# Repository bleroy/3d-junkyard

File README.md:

# 3d-junkyard

A repository of various 3D models and projects.

So far:

* [DecentXE](./DecentXE): a mechanical keyboard for Atari XE computers
* [DecentXL](./DecentXL/): a mechanical keyboard for Atari 600XL and 800XL computers
* [Decent400](./Decent400/): a mechanical keyboard for Atari 400 computers
* [Decent800](./Decent800/): a mechanical keyboard for Atari 800 computers
* [Decent1200](./Decent1200/): a mechanical keyboard for Atari 1200XL computers 
* [Dungeon Master](./DungeonMaster): reverse-engineering Dungeon Master's rendering and running it in a browser
* [Beyond the Jaggi lines](./Jaggilines): reverse-engineering Rescue on Fractalus and running it in a browser
* [JoyKeyMX](./JoyKeyMX): a joypad compatible with Atari 8-bit and 7800 built with Cherry MX compatible switches

## License

All hardware in this repository is licensed under [CERN Open Hardware License v2](https://ohwr.org/cern_ohl_p_v2.pdf).
All software in this repository is licensed under the [MIT license](https://mit-license.org/).
All documentation in this repository is licensed under [Creative Commons Creative Commons Attribution-ShareAlike 4.0 International Public License](https://creativecommons.org/licenses/by-sa/4.0/legalcode).

Full terms can be found in the [LICENSE](./LICENSE) file or on the web sites linked above.

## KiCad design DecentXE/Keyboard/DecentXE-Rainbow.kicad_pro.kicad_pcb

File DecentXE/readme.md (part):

# Decent XE mechanical keyboard replacements for Atari XE computers

Whether you have an old Atari XE computer with a dead keyboard membrane, would like to use a XE keyboard with your favorite PC emulators, or just want to build a more modern XE keyboard, this is the project for you.

There are two versions of the keyboard: modern and vintage. Modern uses brand new MX-compatible key caps, while vintage uses the original Atari key caps and adapts them to modern switches.

There's been a number of previous projects to put a modern keyboard on Atari 8-bit computers. I don't think anyone's done it while preserving the original keycaps though (would love to be proven wrong). Once assembled, you can't tell the difference from an aesthetic point of view... Check this out:

But wait!... That's not all. Since the project started, there's been multiple revisions, adaptations to all kinds of demands from other Atari enthusiasts, and you now have many options to build the keyboard of your dreams...

## Current version

The current revision of the DecentXE modern keyboard is: **rev. 16.1**.

## Can I buy one?

The project is open-source, and I'm encouraging everyone to try to build their own. I do sell kits and assembled keyboards (both modern and vintage) for those who are not comfortable with ordering parts, PCBs or using a soldering iron. If you'd like to order something, [drop me a personal message on AtariAge](https://forums.atariage.com/profile/76850-screamingattheradio/). Keyboards and kits are made to order, so expect several weeks between ordering and receiving.

How expensive is it? It depends on what you're ordering, but this is a made-to-order custom mechanical keyboard, so, not cheap. You can find all the prices [in this thread](https://forums.atariage.com/topic/352558-decent-xe-mechanical-keyboard-for-atari-xe-computers-how-to-order-one/).

## Project history

My first attempt at this was to replace the stem in a [Kailh Box Pink switch](https://novelkeys.com/collections/switches/products/kailh-box-switches?variant=40598132129959) with a 3D-printed version that replaces the regular MX cap footprint with an Atari XE cap footprint. The modified stems were printed with my first printer, an Elegoo Mars 2 Pro. Its 50 micron resolution was essential when replacing such a small and precise part.

This worked great, with switches that were a little more gritty than the originals but still a huge improvement over the mushy XE keyboard I was replacing.

As I made the project public on [Atariage forums](https://forums.atariage.com/topic/324588-atari-130xe-keyboard-rebuild-vintage-keycaps-on-modern-switches), I quickly discovered the key caps I had on my 130XE were only one of two variants, and not the most common at that. I've been supporting both variants, square and circle ever since.

The stabilizers were costar stabilizers for the left shift, which required some creative bending of the vintage stabilizer rod and always remained a little clunky. The space bar rod has a larger diameter and necessitated 3D-printed stabilizers that were, to be frank, terrible. They sorta did the job, just poorly.

The first plate I made was water-jet-cut steel. That was expensive and rusty. I quickly realized after that first attempt that PCB fabrication houses can make aluminum PCBs for cheap. Those are machined rather than laser or water-jet cut, but the quality is perfectly adequate for a fraction of the price. They are just PCBs without circuitry on them. I later learned how other handmade keyboard makers use the same trick, including with regular PCBs, although aluminum is clearly superior for this application.

The first connector I used was an ad-hoc cable made from breadboard jumper wires (I replaced the notoriously hard to source 24 pin Atari connector with pin headers). Based on early feedback, this was quickly replaced with a choice of standard flat cables, to the 1mm pitch 26 pin FFCs used today. Why 26 pins? Because 24 pin FFC connectors and cables don't exist or are hard to source whereas the 26 pin versions are commonly used in DVD players and printers. Also, that gives us two additional lines to separate the backlighting power from the rest, but that in itself came later, at first there was no backlighting and those two additional lines just duplicated the 5V and ground lines, which was just good practice at the time, but turned out to provide that feature for free later without breaking pinout back-compat.

On the side of the Atari motherboard, an adapter was needed that could plug into the original 24 pin connector or be soldered to pin headers, and had a 1mm pitch 26 pin FFC connector on the other side. The main difficulty is that there's very little space between the motherboard and the bottom of the keyboard.

The next breakthrough resulted from re-thinking the constraints:
* Keep compatibility with vintage key caps
* Keep the assembly the same height as the original so everything looks unchanged, including function keys flush to the case

Keeping the same height with MX switches meant replacing internal parts. This is time-consuming and results in lower-quality. What if instead you could work with lower switches that give enough vertical space to build an interface between the switch and the cap? That's what led me to consider low-profile switches. My first choice was to remain with Kailh switches, that I like quite a lot, and I picked Choc v1, specifically Robins that have a clicking behavior similar to Box Pinks. Using adapters instead of replacing internals however also gave the side benefit to allow people to choose the switches they prefer. If you prefer linear or tactile, that's fine.

I made a new version of the PCB for Choc switches which was also the first to have backlighting.

Then there were demands to support more types of low-profile switches to allow for cheaper alternatives to Kailh Chocs.

Around the same time, I had been trying to find reasonably affordable small batch key cap sets to make it possible to build a keyboard without depending on vintage parts. XLFreak is the one who designed and sourced new key caps from [WASD](https://www.wasdkeyboards.com/) (no longer in activity). The very wide space bar doesn't exist on modern keyboards, so we had to shuffle things around. I think the layout that came out of this is better than the original: we get a larger backspace key, an ISO return key, control moves to the left of the smaller 6.5U space bar, break to its right, caps moves to its modern place above left shift. I was able to lay out the PCB so it's compatible with both the vintage and the modern layouts with a single configuration header.

In order to simplify things and have a single unified PCB design, I designed a switch footprint that could accommodate four different kinds of switches: MX, Kailh Choc, Gateron low-pro and RedDragon low-pro.

I also moved the Raspberry Pi Pico connection off the board to a separate USB adapter board since not everybody needed it and it added routing complexity.

It was also a good time to update the stabilizer design. For modern caps, there was no reason not to use the better alternative that are Durock v2 stabilizers. For vintage caps, I wasn't able to swap left switch stabilizers because the way vintage shift keys are built doesn't leave space for 2U Durock v2 stabilizers.

That was where we were with revision 11, which shipped as a pre-order to readers of [the AtariAge forum thread](https://forums.atariage.com/topic/324588-atari-130xe-keyboard-rebuild-vintage-keycaps-on-modern-switches/).

**Revision 12** moved the FFC connector to the top side of the board so it could be assembled at the fab house with the other surface-mount components, and moved to the bottom-right of the board, next to the break key. The FFC cable is now routed to the front between the two halves of the shield.

The power LED is now surface-mount like the backlight LEDs.

The optional function keys (F1-4) pins are now duplicated on a separate header on the top-right of the board to enable easy wiring of those pins to keys placed for example in an extension device.

The adapter that plugs into the motherboard was now smaller, leaving more space above and removing the requirement to replace the Atari keyboard connector and replace it with pin headers (although that was still recommended). The adapter's FFC connector was now moved to the left of the connector instead of above it.

The plate outline has been modified to let more power LED light through.

The silkscreen has been updated to give clearer instructions about configuring the keyboard for vintage or modern modes.

**Revision 13** changes console keys (Help, Start, Select, Option and Reset) to use low-profile switches, which enables thinner 3D-printed key caps that better fit the XE case.

The PCB now has a visual representation of the keyboard matrix with pin numbers, making debugging easier.

The PCB and plate have a consistent Harry Fatt typeface, and each key gets all its glyphs represented, which makes it easier to use the keyboard without caps.

**Revision 14** replaced the adapter and flat cable with a flexible PCB.

**Revision 15** splits the modern and vintage designs. This removes the requirement to have configuration headers and greatly simplifies the layout of the PCBs. I also stopped building assembled vintage keyboards myself with this version, instead focusing on the higher quality modern keyboards. The files for vintage remain available for thos who want to build their own.

**Revision 16**

[x] Power LED switched to red in BOM
[x] Optional red LED diffuser 3D model
[x] Mid-keyboard support 3D model
[x] Back of the board padding 3D model for better fit in the XE case
[x] Console keys have stabilization holes in PCB and plate
[x] Plate covers the whole width of the keyboard and conoles keys area
[x] PCB made 1.75mm deeper to reach the case's fins on the back of the keyboard area
[x] Remove legends from plate front so it's a uniform black between key caps

**Revision 16.1**

[x] Moved the cable slot and connector apart for easier assembly.
[x] Rerouted the whole thing with wider power tracks.

## Options

### Key caps: vintage or modern?

My own original preference was to use the original key caps from a vintage Atari XE computer. They can be scavenged from an existing computer, or from new old stock that's still available at the usual places. The result is, like above, visually indistinguishable from the original keyboard, but feels oh so much better.

XLFreak has been working on new caps in the style of old Atari caps, but that can be produced in small quantities. The nice thing about those is that no adapter is necessary and the end result is an amazing keyboard that is and feels in every way like a great modern keyboard. This is now my preferred option to upgrade Atari XE keyboards.

### Switches

If you're using modern key caps, you may choose any MX-compatible switch. You'll need 5 low-profile Kailh Choc v1 switches for the conole keys.

If you're using vintage caps, you can pick any Kailh Choc v1 low-profile switch.

## Design

The Decent XE project is built on [an original PCB design](./Keyboard/DecentXE-Modern.kicad_pcb), [a custom aluminum plate](./Plate/DecentXE-plate-modern.kicad_pcb), [MX-compatible switches](https://www.kailhswitch.com/mechanical-keyboard-switches/smt-key-switches/box-blue-white-switches-for-mechanical.html), [Kailh Choc v1 low-profile switches](http://www.kailh.com/en/Products/Ks/CS/), custom key caps, 3D printed adapters and Durock v2 and Costar stabilizers.

Here's [a video showing revision B of the project)](https://youtu.be/r8T07Rskkgs):

And here's [another](https://youtu.be/FDqwOca9oRQ/) showing the revision 11 with modern caps:

## Bill of materials

This project is meant to be reproduced. You'll need a few things that are more or less easy to source, so I've made sure to give multiple roads to success and alternatives for most parts.

It's also an approach that could easily be adapted to other vintage computer keyboards, Atari or not. Everything is provided [under an open source license](../LICENSE) so you're encouraged to reproduce and fork the design.

### Atari XE computer

The project is designed around the conservation of the look of Atari XE computers and the integration of the keyboard in its original case. As such, you'll need a host XE computer to receive the end product.

It is also possible however to build and use this keyboard and use it with an emulator on a PC or Mac through a USB adapter. In this way, you can get closer to the original experience even if you don't have access to the original hardware.

* Optimal: Atari XE computer
* Fine: a PC, mac or a MiSTer with [an emulator](https://www.virtualdub.org/altirra.html)

### Key caps

The best result will be obtained with new key caps.

Key caps can be sourced from [ThockFactory](https://thockfactory.com/fr/configurator) or [GoblinTech](https://goblintechkeys.com/collections/60-keycap).

#### ThockFactory

Use the following configuration files in the ThockFactory configurator:

* [Modern layout (white)](./Caps/Atari%20XE%20-%20White%20-%20Thock.json)
* [Modern layout (Falcon)](./Caps/Atari%20XE%20-%20Falcon%20-%20Thock.json)

#### GoblinTech

Use the following templates when ordering from GoblinTech:

* 
* 

#### Vintage

Vintage key caps from an Atari XE computer can also be used to maintain a look that is indistinguishable from the original. Old-new stock of XE keyboards is also currently available without too much trouble and for a reasonable price.

* Optimal: MX-compatible set of key caps
* Fine: vintage set of XE key caps

### Console keys (Help, Start, Select, Option, Reset)

If you're using modern key caps, you'll need to make a choice for console keys.

The best solution is to re-use your vintage console keys with adapters.

Itś also possible to [3D-print your own](./Caps/fn-console-set-choc.stl) and then paint them. I recommend [Tamiya Sea Grey model paint](https://www.tamiyausa.com/shop/acrylic-paint-flat-mini-10ml/acrylic-mini-xf-83-m-sea-gray/) for a pretty good match with the Atari XE case color. You can mask the legends when painting to make them stand out.

* Fine: 3D-printed
* Optimal: vintage function keys on adapters

### Switches

A choice of switches is highly personal and there are many options. Get a sample set if you don't have a preferred kind. You can choose between MX-compatible switches for modern caps and any Kailh Choc v1 switch for conole switches or for the vintage version.

There are three main categories for switches:
* linear (such as reds): the resistance from the switch is about constant as it's pressed.
* tactile (such as browns): there's a slight bump of resistance as the switch is pressed, giving more feedback than linear switches.
* clicky (such as whites): there's a bump in resistance (or it feels like thereś one), accompanied with an audible and satisfying clicking sound.

Console keys should now be mounted on Kailh Choc v1 low-profile switches, so you'll need to buy 5 that match the characteristics of your main keyboard choice (clicky, linear or tactile).

* Optimal: 57 MX-compatible switches of your preferred brand and kind (for modern caps) + 5 Kailh Choc v1 switches for the console keys
* Fine: 62 Kailh Choc v1 low-profile switches (for vintage caps)

### Adapters

The switch adapters link vintage caps to modern switches. As such, you don't need them if you opted for all modern caps. If you're using vintage console keys, you'll need 5 adapters.

The best option today is to simply have the adapters printed, for example by JLCPCB.

Online printing services have become very inexpensive, and the quality of their prints can't be rivalled by any hobbyist printer available today. The trick for small parts such as these adapters is to group them in [batches](./Stems/kailh-choc-to-xe-circle-set.stl) so they count as a single part. I stopped printing locally after the prototyping phase, and am now ordering all my 3D prints from JLCPCB.

If you decide to print them, you'll need a resin printer with a resolution of 50 micrometers (1/20th of a millimeter) or better.

The choice of resin is very important, as the same design on the same printer can give wildly varying qualities of print. For instance, I stay away from all grey Elegoo resins, as I found them to blur the design and be very unreliable. The resin I've had the best results with is Elegoo's [clear red](https://www.elegoo.com/collections/resin/products/elegoo-standard-resin?variant=32365787807792). Resin prints also tend to be brittle, and it's no fun trying to remove a broken leg from inside a switch's stem or a key cap.

There are adapters in the repo for all types of vintage XE caps. You can even generate your own by using [the OpenScad model](./Stems/keeb-stem.scad), which is fully parametric.

* Optimal: order from a fab house such as JLCPCB
    - 7x [set of circle adapters](./Stems/kailh-choc-to-xe-circle-set.stl) or 7x [set of square adapters](Stems/kailh-choc-to-xe-square-set.stl) if you're going full vintage.
    - 5 adapters, circle or square. You can use one of the sets above (10 adapters per set).
* Fine: print your own with a resin printer

I also sell adapters separately from keyboards.

### Board padding (obsolete as of rev. 16)

For the most stable results, you can add two [padding 3D-printed parts](./Stabilizers/HeightPadding.stl) on top of the main board at the bottom left and right:

Those can be printed on any 3D printer as they don't require a lot of precision.

[Additional padding](./Misc/XE-rev-before-16-depth-padding.stl) can be added to the back of the board to prevent the keyboard from moving to the back of the computer.

### Mid-keyboard support

While the XE case provides some support to the middle of the keyboard with a column, pressing the console keys can still cause some bending of the board. To prevent that, [support](./Misc/XE-mid-keeb-support.stl) can be added to the left of the console keys.

### Power LED coloring

If you have a board with a white power LED and your XE case has a transparent LED window, you can still make thepower LED shine red using a [LED diffuser](./Misc/LED-red-lens.stl) printed in transparent red.

### Stabilizers

If you're using modern caps, just use Durock v2 stabilizers for backspace, Return, left shift and the space bar.

The Atari XE keyboard has stabilizers on the left SHIFT key and on the space bar. Some versions also have stabilizers on control and right shift, but anything 2U and smaller can work well without stabilizers.

The left shift stabilizer is made with a standard metal bar that fits in standard costar stabilizers, for which the vintage plate is designed. There are two possible orientations for the costar stabilizers that work best for the circle and square variants of vintage key caps. Those stabilizers can be bought for a very reasonable price from many places.

The vintage space bar can use Durock v2 stabilizers, for which I've made adapters for both types of vintage Atari space bars.

* Optimal (modern caps): 1x 6.5U and 3x 2U Durock v2 stabilizers
* Fine (vintage caps):
    * Vintage Atari XE left shift stabilizer metal part
    * 2x standard costar stabilizers
    * 1x 6.5U Durock v2 stabilizer set
    * 3D-printed stabilizer adapters [for circle](./Stabilizers/durock-v2-spacebar-circle-adapter.stl) or [square](./Stabilizers/durock-v2-spacebar-square-adapter.stl)

### Main board

The [DecentXE KiCad project](./Keyboard/DecentXE-Modern.kicad_pcb) should have everything you need to order a 2 layer PCB from any manufacturing house. The board requires surface-mount diodes, LEDs, resistors and connectors that are best assembled at the fabrication house: nobody wants to solder 62 of the same very tiny components by hand. I think. I don't.

* Optimal:
    - [DecentXE Modern main board Gerber files](./Keyboard//production/Decent_XE_Keyboard_-_Modern_16.1.zip)
    - [DecentXE Modern BOM file](./Keyboard/production/Decent_XE_Keyboard_-_Modern_16.1-bom.csv)
    - [DecentXE Modern Position file](./Keyboard/production/Decent_XE_Keyboard_-_Modern_16.1-positions.csv)
* Fine:
    - [DecentXE Vintage main board Gerber files](./Keyboard//production/Decent_XE_Keyboard_-_Vintage_15.zip)
    - [DecentXE Vintage BOM file](./Keyboard/production/Decent_XE_Keyboard_-_Vintage_15-bom.csv)
    - [DecentXE Vintage Position file](./Keyboard/production/Decent_XE_Keyboard_-_Vintage_15-positions.csv)

### Plate

While it is possible to build and operate a keyboard without a plate, it will not be as nicely aligned and won't feel as solid as it would with a proper plate.

In terms of weight, the keyboard assembled with an aluminum plate is about 430g.

* Optimal: 1.6mm aluminum PCB. Aluminum PCBs can be made for similar prices as regular PCBs nowadays, and that constitutes the best price / performance compromise currently available.
    - [DecentXE Modern aluminum plate Gerber files](./Plate/production/Decent_XE_Keyboard_Plate_-_Modern_16m.zip)
    - [DecentXE Vintage aluminum plate Gerber files](./Plate/production/Decent_XE_Keyboard_Plate_Vintage_15v.zip)
* Great but expensive: laser-cut or waterjet-cut metal
* Not fine: laser-cut acrylic. Really, don't even try, it'll shatter. Some other laser-cut plastics may be OK, but I can't help you with that, I don't know.

When using vintage caps, you may need to add some spacers between the board and the plate while building, in addition to the switches themselves. I've been using stacked washers.

There's a smaller, 3D-printed plate for the console keys that also adjusts the height of the switches relative to the PCB:

* [Console key plate](./Stabilizers/LowProRaiserPlate.stl)

### Connector

The original Atari XE keyboard's connector was just a part of the mylar membrane. We need a replacement for that. Note that the clearance between the Atari XE motherboard and the bottom of the keyboard is very small at about 16mm.

The current solution is a custom flexible PCB that can plug directly into the Atari motherboard connector, and is compatible with a modern 1mm 26 positions surface-mounted connector on the other side:

If your Atari connector is damaged, or you don't have one, it's also possible to solder [an adapter](../Atari130MX/Atari130MX-adapter/Atari130MX-adapter.kicad_pro) and use a standard 1mm pitch 26 position flat cable.

* Optimal:
    * [Flexible PCB](../DecentXL/DecentXL-Cable/production/DecentXL_Flexible_Cable_2.zip).
* Fine:
    * [FFC 26 position 1mm Type A](https://www.digikey.com/en/products/detail/adafruit-industries-llc/5386/16129671?s=N4IgTCBcDaIIwFsEAIAOBLALgYwBbLADY10A7EAXQF8g) (contacts on the same side on both ends) ribbon cable, 15cm at least.  Here's also [an Amazon source](https://www.amazon.com/uxcell-Flexible-Cable-Ribbon-Player/dp/B07RWRX6YT/r).
    * [XE keyboard Adapter](../Atari130MX/Fabrication/DecentXE-adapter.zip)
    * 1x24 2.54mm pin headers

## Fabrication and assembly instruction

Once you've sourced all the components, it's time to assemble. The following instructions attempt to reflect all the choices you may have made in selecting components.

Jan Beta has a great video where he shows the full assembly process (the mistake he makes with the config jumpers can no longer be made: those are gone from the design).

### Printing console caps and adapters (optional)

There are two known shapes of vintage key caps, requiring distinct adapters. The first type of key cap has square stems, while the second has circular stems.

In this repository, you'll find [OpenScad](./Stems/keeb-stem.scad) and [STL](./Stems) files for [both](./Stems/kailh-choc-to-xe-circle-set.stl) [types](./Stems/kailh-choc-to-xe-circle-set.stl) of stems. If you need to modify anything about the stems, you'd need to regenerate the STL from the OpenScad file. There is [a single OpenScad file](./Stems/keeb-stem.scad) that covers both types of stems through configuration. Otherwise, just send the STL file to your 3D printing manufacturer.

You'll need 62 adapters total for the whole vintage keyboard, and only 5 for modern if you want to re-use your vintage console keys.

### Optional: replace the Atari connector

If you lack the original Atari connector on your motherboard (rare), you may want to use an adapter and solder that in.

### Installing a modern keyboard (assembled)

I do sell assembled modern keyboards, but you still need to get those into your Atari. This section goes through the details of doing that.

The FFC cable should already be attached to the keyboard.

[skip to the common section](#common-section-inserting-the-adapter)

### Installing a vintage keyboard (assembled)

Use a key cap extractor to remove the keys from your vintage keyboard (a key extractor is the best way to make sure you don't damage the caps). Make sure to be especially gentle if you have the square variant, those break easily.

Put the two space bar stabilizer adapters into your vintage space bar. You can set aside the old metal rod for this key, you won't need it. The alignment of the stabilizers and the adapters is not always perfect. If that's a problem in your build, you can try to adjust the OpenScad model to move the footprint and better align with your space bar. Even with good alignment, I recommend salvaging the spring from the original keyboard and inserting it into the new keyboard. It does make a big difference for vintage builds.

Remove the stabilizer rod for your left shift key. You'll need to slightly bend this so it can go around the new switch and into the new stabilizer. This may require some fiddling. In the worst case, the left shift stabilizer can be omitted if you can't find a way to make it work. This is my least favorite part of those keyboards...

Assemble the caps back onto the new keyboard by gently pressing them into place.

[skip to the common section](#common-section-inserting-the-adapter)

### Modern keyboard (kit)

If you ordered a kit or parts from the BOM, there is a specific order in which you should assemble.

#### Assemble the Durock stabilizers

The stabilizers consist of a larger part that has the threaded part, a smaller part that slides into the previous one, a metal bar linking two assemblies of the two previous parts, and some hardware. The stabilizers are best assembled in this order: slide the smaller part into the larger one (make sure you orient it properly), then insert one end of the metal rod into that assembly and push it into place so it clicks and is properly secured. Once you've done that with both ends of the stabilizer, you should be able to verify both ends lift together and with no friction (some people like to lube their stabilizers for added smoothness).

Once the stabilizers are assembled, you can put them in their respective places on the top side of the PCB. Insert the bottom, non-threaded part first, try to lay the stabilizer's surface flat on the PCB, and push the top threaded part into place. This usually moves the other end a bit, so make sure both ends are properly inserted all the way into the holes in the PCB.

Turn the PCB over. Optionally position a small washers around each of the screw holes for the stabilizers. Secure the stabilizer into place with a screw. Repeat this for the space stabilizer, the left shift, the delete key and the return key.

#### Solder the console key switches

The console key switches go *under* the plate, and as such need to be soldered before the other switches are inserted into the plate and soldered.

#### Add the cable

Insert the flexible PCB from below the PCB into its slot through the PCB, so the contacts are on the bottom and can face the board.

Pull the two tabs for the connector, then insert the contacts into the connector, pushing the cable as far as it will go. Push the tabs back in.

At this point, I usually test continuity between a few of the solder points on the board to the other end of the connector, in order to check the cable is properly inserted and secure.

#### Mount the switches onto the plate

Insert switches into the aluminum plate with the LED window to the back and the pins to the front. The exception to this is the modern return key that should have its LED window to the left and pins to the right.

Note that the console keys do not have a place on the plate. That's because they use low-profile switches that wouldn't reach the height of the plate. We'll assemble those later.

#### Get the plate and PCB together

After making sure all the switch pins are vertical and none are bent out of place, carefully align the plate and switches with the stabilizers and the PCB. Slowly and carefully complete that assembly, making sure no pins get bent. Once that is done, the plate and PCB should be a few millimeters apart, more or less evenly spaced across the whole surface. You may want  to secure them together with tape or clothespins until you've soldered enough of them.

#### Solder the switches onto the PCB.

Solder each switch onto the PCB.

Once you've done all the full-size switches, insert the low-profile switches for the console keys into their 3D-printed plate, then align that to the PCB. Solder the switches.

Even after soldering, you can make small adjustments by melting the solder around one of the pins and carefully moving the switch, then reflow the other pin of the same switch to relieve constraints or further adjust.

[skip to the common section](#common-section-inserting-the-adapter)

### Vintage keyboard (kit)

If you ordered a kit or are building one from parts from the BOM, there is a specific order in which you should assemble.

#### Assemble the space stabilizer

Assemble the space stabilizer. The stabilizers consist of a larger part that has the threaded part, a smaller part that slides into the previous one, a metal bar linking two assemblies of the two previous parts, and some hardware. The stabilizers are best assembled in this order: slide the smaller part into the larger one (make sure you orient it properly), then insert one end of the metal rod into that assembly and push it into place so it clicks and is properly secured. Once you've done that with both ends of the stabilizer, you should be able to verify both ends lift together and with no friction (some people like to lube their stabilizers by the way).

Once the stabilizer is assembled, you can put both ends in their respective places on the top side of the PCB. Insert the bottom, non-threaded part first, try to lay the stabilizer's surface flat on the PCB, and push the top threaded part into place. This usually moves the other end a bit, so make sure both ends are properly inserted all the way into the holes in the PCB.

Turn the PCB over. Optionally position a small washers around each of the screw holes for the stabilizers. Secure the stabilizer with a screw.

#### Add the cable

Insert the flexible PCB from below the PCB into its slot through the PCB, so the contacts are on the bottom and can face the board.

Pull the two tabs for the connector, then insert the contacts into the connector, pushing the cable as far as it will go. Push the tabs back in.

At this point, I usually test continuity between a few of the solder points on the board to the other end of the connector, in order to check the cable is properly inserted and secure.

#### Mount the switches onto the plate

Insert switches into the aluminum plate with the LED window to the back and the pins to the front.

#### Get the plate and PCB together

After making sure all the switch pins are vertical and none are bent out of place, carefully align the plate and switches with the stabilizers and the PCB. Slowly and carefully complete that assembly, making sure no pins get bent.

Once that is done, the plate and PCB should be a few millimeters apart, more or less evenly spaced across the whole surface. Low-profile switches have a tendency to not attach to the plate as well as full-sized switches, so don't worry if some of these fall out during assembly, you'll have a chance to set them back in later. At this point, you want to have enough switches in place to ensure proper alignment.

Another thing with low-profile switches is that they're not as good at maintaining the distance between PCB and plate. To make that distane more even with the distance imposed by the space stabilizer, there are two holes for M2 screws at the top of the plate and main board. Use three M2 nuts to keep the correct distance between the plate and PCB. Secure everything from the top with one final nut.

#### Assemble the left shift stabilizer

The left shift stabilizer is more problematic and potentially the most frustrating part of this build. Worst case, it may be fine to just omit this stabilizer because if improperly installed it can make things worse. The stabilizer consists of two plastic parts that should fit into slots around the switch's position. Depending on whether you have circle or square caps, it should be installed upside up or upside down. Those stabilizers are very tricky to put in place. Once they are in place, you'll need (later, we'll get back to that) to get the metal rod from your vintage left shift, remove it, then bend it slightly so it can go around the switch and still be inserted into the new stabilizer. I'm not kidding when I say this is frustrating.

#### Solder the switches

Solder the switches onto the PCB. The Choc switches will barely stick out on the back of the PCB. This is normal, but makes soldering a little more difficult. Give the iron enough time to heat up the vias, the solder and the pins and create a proper join, even if that join ends up relatively flat.

Dont's forget the console keys. Since those do not mount on the plate, use a 3D-printed console key plate to align the switches precisely and keep the switches at the correct height.

Even after soldering, you can make small adjustments by melting the solder around one of the pins and carefully moving the switch, then reflow the other pin of the same switch to relieve constraints or further adjust.

### Common section: inserting the cable

Remove your existing keyboard, pulling the membrane connector carefully using both hands to avoid accidentally folding it.

Insert the flexible PCB into the connector on the motherboard.

Add the height padding on top of your keyboard's main PCB, to the bottom left and right.

You can now power your computer. The power LED on the keyboard should go on and the backlighting should too (this is a good time to set the potentiometer on the bottom left to a brightness level you're comfortabel with). 

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
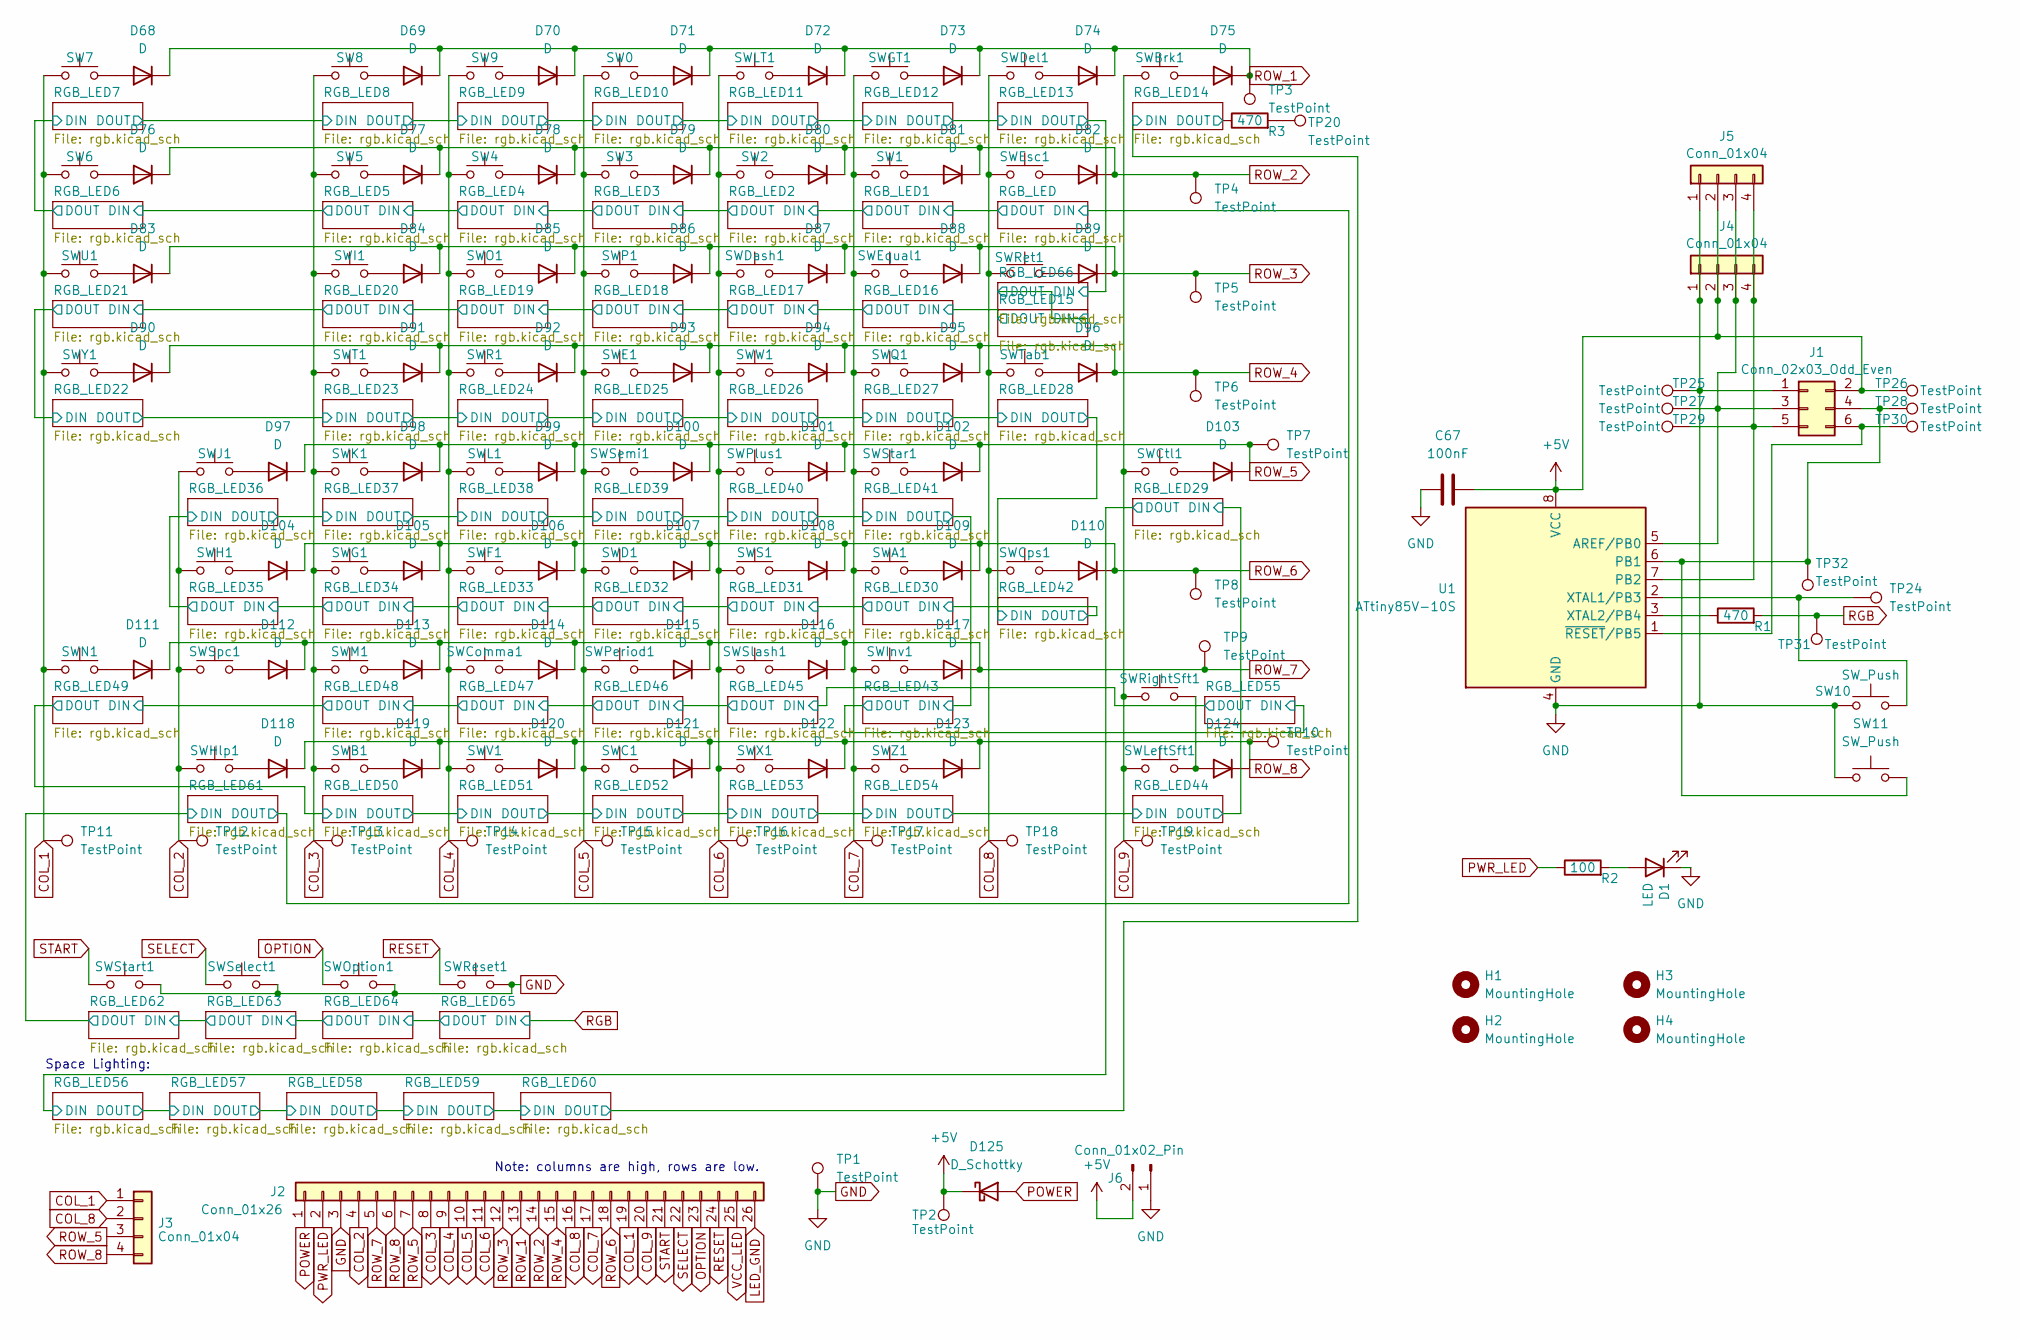
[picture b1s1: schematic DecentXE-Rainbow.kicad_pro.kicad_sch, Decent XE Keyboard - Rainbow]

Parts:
C67: 100nF; C_0402_1005Metric; LCSC Part # C1525
D1: LED; LED1206-RD_RED_XL-3216SURC-FB; LCSC Part # C559117
D68, D69, D70, D71, D72, D73, D74, D75, D76, D77, D78, D79, D80, D81, D82, D83, D84, D85, D86, D87, D88, D89, D90, D91, D92, D93, D94, D95, D96, D97, D98, D99, D100, D101, D102, D103, D104, D105, D106, D107, D108, D109, D110, D111, D112, D113, D114, D115, D116, D117, D118, D119, D120, D121, D122, D123, D124: D; D_SOD-123; LCSC Part # C81598
D125: D_Schottky; D_SOD-123; LCSC Part # C8598
H1, H2, H3, H4: MountingHole; MountingHole_3.2mm_M3
J1: Conn_02x03_Odd_Even; PinHeader_2x03_P2.54mm_Vertical
J2: Conn_01x26; Molex_200528-0260_1x26-1MP_P1.00mm_Horizontal; LCSC Part # C2915299
J3, J4, J5: Conn_01x04; PinHeader_1x04_P2.54mm_Vertical
J6: Conn_01x02_Pin; PinHeader_1x02_P2.54mm_Vertical
R1, R3: 470; R_0402_1005Metric; LCSC Part # C25117
R2: 100; R_0402_1005Metric; LCSC Part # C25076
SW0, SW1, SW2, SW3, SW4, SW5, SW6, SW7, SW8, SW9: SW_Push; SW_Cherry_MX_1.00u_PCB
SW10, SW11: SW_Push; SW_PUSH_6mm
SWA1: SW_Push; SW_Cherry_MX_1.00u_PCB
SWB1: SW_Push; SW_Cherry_MX_1.00u_PCB
SWBrk1: SW_Push; SW_Cherry_MX_1.25u_PCB
SWC1: SW_Push; SW_Cherry_MX_1.00u_PCB
SWComma1: SW_Push; SW_Cherry_MX_1.00u_PCB
SWCps1: SW_Push; SW_Cherry_MX_1.75u_PCB
SWCtl1: SW_Push; SW_Cherry_MX_1.25u_PCB
SWD1: SW_Push; SW_Cherry_MX_1.00u_PCB
SWDash1: SW_Push; SW_Cherry_MX_1.00u_PCB
SWDel1: SW_Push; SW_Cherry_MX_2.00u_PCB
SWE1: SW_Push; SW_Cherry_MX_1.00u_PCB
SWEqual1: SW_Push; SW_Cherry_MX_1.00u_PCB
SWEsc1: SW_Push; SW_Cherry_MX_1.00u_PCB
SWF1: SW_Push; SW_Cherry_MX_1.00u_PCB
SWG1: SW_Push; SW_Cherry_MX_1.00u_PCB
SWGT1: SW_Push; SW_Cherry_MX_1.00u_PCB
SWH1: SW_Push; SW_Cherry_MX_1.00u_PCB
SWHlp1: SW_Push; Choc-1-50U-Atari-Console
SWI1: SW_Push; SW_Cherry_MX_1.00u_PCB
SWInv1: SW_Push; SW_Cherry_MX_1.00u_PCB
SWJ1: SW_Push; SW_Cherry_MX_1.00u_PCB
SWK1: SW_Push; SW_Cherry_MX_1.00u_PCB
SWL1: SW_Push; SW_Cherry_MX_1.00u_PCB
SWLT1: SW_Push; SW_Cherry_MX_1.00u_PCB
SWLeftSft1: SW_Push; SW_Cherry_MX_2.25u_PCB
SWM1: SW_Push; SW_Cherry_MX_1.00u_PCB
SWN1: SW_Push; SW_Cherry_MX_1.00u_PCB
SWO1: SW_Push; SW_Cherry_MX_1.00u_PCB
SWOption1: SW_Push; Choc-1-50U-Atari-Console
SWP1: SW_Push; SW_Cherry_MX_1.00u_PCB
SWPeriod1: SW_Push; SW_Cherry_MX_1.00u_PCB
SWPlus1: SW_Push; SW_Cherry_MX_1.00u_PCB
SWQ1: SW_Push; SW_Cherry_MX_1.00u_PCB
SWR1: SW_Push; SW_Cherry_MX_1.00u_PCB
SWReset1: SW_Push; Choc-1-50U-Atari-Console
SWRet1: SW_Push; SW_Cherry_MX_ISOEnter_PCB
SWRightSft1: SW_Push; SW_Cherry_MX_1.75u_PCB
SWS1: SW_Push; SW_Cherry_MX_1.00u_PCB
SWSelect1: SW_Push; Choc-1-50U-Atari-Console
SWSemi1: SW_Push; SW_Cherry_MX_1.00u_PCB
SWSlash1: SW_Push; SW_Cherry_MX_1.00u_PCB
SWSpc1: SW_Push; SW_Cherry_MX_6.25u_PCB
SWStar1: SW_Push; SW_Cherry_MX_1.00u_PCB
SWStart1: SW_Push; Choc-1-50U-Atari-Console
SWT1: SW_Push; SW_Cherry_MX_1.00u_PCB
SWTab1: SW_Push; SW_Cherry_MX_1.50u_PCB
SWU1: SW_Push; SW_Cherry_MX_1.00u_PCB
SWV1: SW_Push; SW_Cherry_MX_1.00u_PCB
SWW1: SW_Push; SW_Cherry_MX_1.00u_PCB
SWX1: SW_Push; SW_Cherry_MX_1.00u_PCB
SWY1: SW_Push; SW_Cherry_MX_1.00u_PCB
SWZ1: SW_Push; SW_Cherry_MX_1.00u_PCB
TP1, TP2, TP3, TP4, TP5, TP6, TP7, TP8, TP9, TP10, TP11, TP12, TP13, TP14, TP15, TP16, TP17, TP18, TP19, TP20, TP24, TP25, TP26, TP27, TP28, TP29, TP30, TP31, TP32: TestPoint; TestPoint_THTPad_D2.0mm_Drill1.0mm
U1: ATtiny85V-10S; SOIC-8_5.3x5.3mm_P1.27mm; LCSC Part # C31540447

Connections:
+5V: C67.2, D125.1 (K), J1.2, J4.2, J5.2, J6.2, TP2.1 (1_1), TP26.1 (1_1), U1.8 (VCC); also elsewhere on the board
/RGB_LED14/DOUT: R3.1; also elsewhere on the board
COL_1: J2.19, J3.1, SW6.1, SW7.1, SWN1.1, SWU1.1, SWY1.1, TP11.1 (1_1)
COL_2: J2.4, SWH1.1, SWHlp1.1, SWJ1.1, SWSpc1.1, TP12.1 (1_1)
COL_3: J2.8, SW5.1, SW8.1, SWB1.1, SWG1.1, SWI1.1, SWK1.1, SWM1.1, SWT1.1, TP13.1 (1_1)
COL_4: J2.9, SW4.1, SW9.1, SWComma1.1, SWF1.1, SWL1.1, SWO1.1, SWR1.1, SWV1.1, TP14.1 (1_1)
COL_5: J2.10, SW0.1, SW3.1, SWC1.1, SWD1.1, SWE1.1, SWP1.1, SWPeriod1.1, SWSemi1.1, TP15.1 (1_1)
COL_6: J2.11, SW2.1, SWDash1.1, SWLT1.1, SWPlus1.1, SWS1.1, SWSlash1.1, SWW1.1, SWX1.1, TP16.1 (1_1)
COL_7: J2.17, SW1.1, SWA1.1, SWEqual1.1, SWGT1.1, SWInv1.1, SWQ1.1, SWStar1.1, SWZ1.1, TP17.1 (1_1)
COL_8: J2.16, J3.2, SWCps1.1, SWDel1.1, SWEsc1.1, SWRet1.1, SWTab1.1, TP18.1 (1_1)
COL_9: J2.20, SWBrk1.1, SWCtl1.1, SWLeftSft1.1, SWRightSft1.1, TP19.1 (1_1)
GND: C67.1, D1.1 (K), J1.1, J2.3, J4.1, J5.1, J6.1, SW10.1, SW11.1, SWOption1.2, SWReset1.2, SWSelect1.2, SWStart1.2, TP1.1 (1_1), TP25.1 (1_1), U1.4 (GND); also elsewhere on the board
LED_GND: J2.26
unnamed: D1.2 (A), R2.2
unnamed: D68.2 (A), SW7.2
unnamed: D69.2 (A), SW8.2
unnamed: D70.2 (A), SW9.2
unnamed: D71.2 (A), SW0.2
unnamed: D72.2 (A), SWLT1.2
unnamed: D73.2 (A), SWGT1.2
unnamed: D74.2 (A), SWDel1.2
unnamed: D75.2 (A), SWBrk1.2
unnamed: D76.2 (A), SW6.2
unnamed: D77.2 (A), SW5.2
unnamed: D78.2 (A), SW4.2
unnamed: D79.2 (A), SW3.2
unnamed: D80.2 (A), SW2.2
unnamed: D81.2 (A), SW1.2
unnamed: D82.2 (A), SWEsc1.2
unnamed: D83.2 (A), SWU1.2
unnamed: D84.2 (A), SWI1.2
unnamed: D85.2 (A), SWO1.2
unnamed: D86.2 (A), SWP1.2
unnamed: D87.2 (A), SWDash1.2
unnamed: D88.2 (A), SWEqual1.2
unnamed: D89.2 (A), SWRet1.2
unnamed: D90.2 (A), SWY1.2
unnamed: D91.2 (A), SWT1.2
unnamed: D92.2 (A), SWR1.2
unnamed: D93.2 (A), SWE1.2
unnamed: D94.2 (A), SWW1.2
unnamed: D95.2 (A), SWQ1.2
unnamed: D96.2 (A), SWTab1.2
unnamed: D97.2 (A), SWJ1.2
unnamed: D98.2 (A), SWK1.2
unnamed: D99.2 (A), SWL1.2
unnamed: D100.2 (A), SWSemi1.2
unnamed: D101.2 (A), SWPlus1.2
unnamed: D102.2 (A), SWStar1.2
unnamed: D103.2 (A), SWCtl1.2
unnamed: D104.2 (A), SWH1.2
unnamed: D105.2 (A), SWG1.2
unnamed: D106.2 (A), SWF1.2
unnamed: D107.2 (A), SWD1.2
unnamed: D108.2 (A), SWS1.2
unnamed: D109.2 (A), SWA1.2
unnamed: D110.2 (A), SWCps1.2
unnamed: D111.2 (A), SWN1.2
unnamed: D112.2 (A), SWSpc1.2
unnamed: D113.2 (A), SWM1.2
unnamed: D114.2 (A), SWComma1.2
unnamed: D115.2 (A), SWPeriod1.2
unnamed: D116.2 (A), SWSlash1.2
unnamed: D117.2 (A), SWInv1.2
unnamed: D118.2 (A), SWHlp1.2
unnamed: D119.2 (A), SWB1.2
unnamed: D120.2 (A), SWV1.2
unnamed: D121.2 (A), SWC1.2
unnamed: D122.2 (A), SWX1.2
unnamed: D123.2 (A), SWZ1.2
unnamed: D124.2 (A), SWLeftSft1.2, SWRightSft1.2
unnamed: J1.3, J4.3, J5.3, TP27.1 (1_1), U1.5 (AREF/PB0)
unnamed: J1.4, SW11.2, TP28.1 (1_1), TP32.1 (1_1), U1.6 (PB1)
unnamed: J1.5, J4.4, J5.4, TP29.1 (1_1), U1.7 (PB2)
unnamed: J1.6, TP30.1 (1_1), U1.1 (~RESET/PB5)
unnamed: R3.2, TP20.1 (1_1)
unnamed: SW10.2, TP24.1 (1_1), U1.2 (XTAL1/PB3)
unnamed: R1.1, U1.3 (XTAL2/PB4)
OPTION: J2.23, SWOption1.1
POWER: D125.2 (A), J2.1
PWR_LED: J2.2, R2.1
RESET: J2.24, SWReset1.1
RGB: R1.2, TP31.1 (1_1); also elsewhere on the board
ROW_1: D68.1 (K), D69.1 (K), D70.1 (K), D71.1 (K), D72.1 (K), D73.1 (K), D74.1 (K), D75.1 (K), J2.13, TP3.1 (1_1)
ROW_2: D76.1 (K), D77.1 (K), D78.1 (K), D79.1 (K), D80.1 (K), D81.1 (K), D82.1 (K), J2.14, TP4.1 (1_1)
ROW_3: D83.1 (K), D84.1 (K), D85.1 (K), D86.1 (K), D87.1 (K), D88.1 (K), D89.1 (K), J2.12, TP5.1 (1_1)
ROW_4: D90.1 (K), D91.1 (K), D92.1 (K), D93.1 (K), D94.1 (K), D95.1 (K), D96.1 (K), J2.15, TP6.1 (1_1)
ROW_5: D97.1 (K), D98.1 (K), D99.1 (K), D100.1 (K), D101.1 (K), D102.1 (K), D103.1 (K), J2.7, J3.3, TP7.1 (1_1)
ROW_6: D104.1 (K), D105.1 (K), D106.1 (K), D107.1 (K), D108.1 (K), D109.1 (K), D110.1 (K), J2.18, TP8.1 (1_1)
ROW_7: D111.1 (K), D112.1 (K), D113.1 (K), D114.1 (K), D115.1 (K), D116.1 (K), D117.1 (K), J2.5, TP9.1 (1_1)
ROW_8: D118.1 (K), D119.1 (K), D120.1 (K), D121.1 (K), D122.1 (K), D123.1 (K), D124.1 (K), J2.6, J3.4, TP10.1 (1_1)
SELECT: J2.22, SWSelect1.1
START: J2.21, SWStart1.1
VCC_LED: J2.25

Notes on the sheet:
Space Lighting:
Note: columns are high, rows are low.

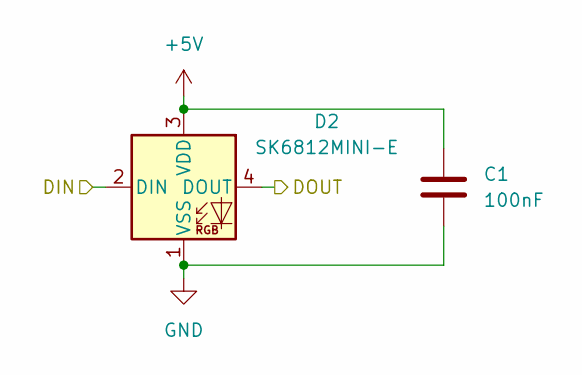
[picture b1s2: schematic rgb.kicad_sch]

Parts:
C1: 100nF; C_0402_1005Metric; LCSC Part # C1525
D2: SK6812MINI-E; LED_SK6812MINI-E_3.2x2.8mm_P1.5mm_ReverseMount; LCSC Part # C5378731

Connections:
+5V: C1.1, D2.3 (VDD); also elsewhere on the board
/RGB_LED/DIN: D2.2 (DIN); also elsewhere on the board
/RGB_LED/DOUT: D2.4 (DOUT); also elsewhere on the board
GND: C1.2, D2.1 (VSS); also elsewhere on the board

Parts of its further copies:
C2, C3, C4, C5, C6, C7, C8, C9, C10, C11, C12, C13, C14, C15, C16, C17, C18, C19, C20, C21, C22, C23, C24, C25, C26, C27, C28, C29, C30, C31, C32, C33, C34, C35, C36, C37, C38, C39, C40, C41, C42, C43, C44, C45, C46, C47, C48, C49, C50, C51, C52, C53, C54, C55, C56, C57, C58, C59, C60, C61, C62, C63, C64, C65, C66, C68: 100nF; C_0402_1005Metric; LCSC Part # C1525
D3, D4, D5, D6, D7, D8, D9, D10, D11, D12, D13, D14, D15, D16, D17, D18, D19, D20, D21, D22, D23, D24, D25, D26, D27, D28, D29, D30, D31, D32, D33, D34, D35, D36, D37, D38, D39, D40, D41, D42, D43, D44, D45, D46, D47, D48, D49, D50, D51, D52, D53, D54, D55, D56, D57, D58, D59, D60, D61, D62, D63, D64, D65, D66, D67, D126: SK6812MINI-E; LED_SK6812MINI-E_3.2x2.8mm_P1.5mm_ReverseMount; LCSC Part # C5378731

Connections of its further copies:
+5V: C2.1, C3.1, C4.1, C5.1, C6.1, C7.1, C8.1, C9.1, C10.1, C11.1, C12.1, C13.1, C14.1, C15.1, C16.1, C17.1, C18.1, C19.1, C20.1, C21.1, C22.1, C23.1, C24.1, C25.1, C26.1, C27.1, C28.1, C29.1, C30.1, C31.1, C32.1, C33.1, C34.1, C35.1, C36.1, C37.1, C38.1, C39.1, C40.1, C41.1, C42.1, C43.1, C44.1, C45.1, C46.1, C47.1, C48.1, C49.1, C50.1, C51.1, C52.1, C53.1, C54.1, C55.1, C56.1, C57.1, C58.1, C59.1, C60.1, C61.1, C62.1, C63.1, C64.1, C65.1, C66.1, C68.1, D3.3 (VDD), D4.3 (VDD), D5.3 (VDD), D6.3 (VDD), D7.3 (VDD), D8.3 (VDD), D9.3 (VDD), D10.3 (VDD), D11.3 (VDD), D12.3 (VDD), D13.3 (VDD), D14.3 (VDD), D15.3 (VDD), D16.3 (VDD), D17.3 (VDD), D18.3 (VDD), D19.3 (VDD), D20.3 (VDD), D21.3 (VDD), D22.3 (VDD), D23.3 (VDD), D24.3 (VDD), D25.3 (VDD), D26.3 (VDD), D27.3 (VDD), D28.3 (VDD), D29.3 (VDD), D30.3 (VDD), D31.3 (VDD), D32.3 (VDD), D33.3 (VDD), D34.3 (VDD), D35.3 (VDD), D36.3 (VDD), D37.3 (VDD), D38.3 (VDD), D39.3 (VDD), D40.3 (VDD), D41.3 (VDD), D42.3 (VDD), D43.3 (VDD), D44.3 (VDD), D45.3 (VDD), D46.3 (VDD), D47.3 (VDD), D48.3 (VDD), D49.3 (VDD), D50.3 (VDD), D51.3 (VDD), D52.3 (VDD), D53.3 (VDD), D54.3 (VDD), D55.3 (VDD), D56.3 (VDD), D57.3 (VDD), D58.3 (VDD), D59.3 (VDD), D60.3 (VDD), D61.3 (VDD), D62.3 (VDD), D63.3 (VDD), D64.3 (VDD), D65.3 (VDD), D66.3 (VDD), D67.3 (VDD), D126.3 (VDD); also elsewhere on the board
/RGB_LED1/DOUT: D3.4 (DOUT), D4.2 (DIN)
/RGB_LED2/DOUT: D4.4 (DOUT), D5.2 (DIN)
/RGB_LED3/DOUT: D5.4 (DOUT), D6.2 (DIN)
/RGB_LED4/DOUT: D6.4 (DOUT), D7.2 (DIN)
/RGB_LED5/DOUT: D7.4 (DOUT), D8.2 (DIN)
/RGB_LED6/DOUT: D8.4 (DOUT), D9.2 (DIN)
/RGB_LED7/DOUT: D9.4 (DOUT), D10.2 (DIN)
/RGB_LED8/DOUT: D10.4 (DOUT), D11.2 (DIN)
/RGB_LED10/DIN: D11.4 (DOUT), D12.2 (DIN)
/RGB_LED10/DOUT: D12.4 (DOUT), D13.2 (DIN)
/RGB_LED11/DOUT: D13.4 (DOUT), D14.2 (DIN)
/RGB_LED12/DOUT: D14.4 (DOUT), D15.2 (DIN)
/RGB_LED13/DOUT: D15.4 (DOUT), D126.2 (DIN)
/RGB_LED14/DIN: D16.2 (DIN), D62.4 (DOUT)
/RGB_LED14/DOUT: D16.4 (DOUT); also elsewhere on the board
/RGB_LED15/DIN: D17.2 (DIN), D126.4 (DOUT)
/RGB_LED15/DOUT: D17.4 (DOUT), D18.2 (DIN)
/RGB_LED16/DOUT: D18.4 (DOUT), D19.2 (DIN)
/RGB_LED17/DOUT: D19.4 (DOUT), D20.2 (DIN)
/RGB_LED18/DOUT: D20.4 (DOUT), D21.2 (DIN)
/RGB_LED19/DOUT: D21.4 (DOUT), D22.2 (DIN)
/RGB_LED20/DOUT: D22.4 (DOUT), D23.2 (DIN)
/RGB_LED21/DOUT: D23.4 (DOUT), D24.2 (DIN)
/RGB_LED22/DOUT: D24.4 (DOUT), D25.2 (DIN)
/RGB_LED23/DOUT: D25.4 (DOUT), D26.2 (DIN)
/RGB_LED24/DOUT: D26.4 (DOUT), D27.2 (DIN)
/RGB_LED25/DOUT: D27.4 (DOUT), D28.2 (DIN)
/RGB_LED26/DOUT: D28.4 (DOUT), D29.2 (DIN)
/RGB_LED27/DOUT: D29.4 (DOUT), D30.2 (DIN)
/RGB_LED28/DOUT: D30.4 (DOUT), D44.2 (DIN)
/RGB_LED29/DIN: D31.2 (DIN), D46.4 (DOUT)
/RGB_LED29/DOUT: D31.4 (DOUT), D58.2 (DIN)
/RGB_LED30/DIN: D32.2 (DIN), D44.4 (DOUT)
/RGB_LED30/DOUT: D32.4 (DOUT), D33.2 (DIN)
/RGB_LED31/DOUT: D33.4 (DOUT), D34.2 (DIN)
/RGB_LED32/DOUT: D34.4 (DOUT), D35.2 (DIN)
/RGB_LED33/DOUT: D35.4 (DOUT), D36.2 (DIN)
/RGB_LED34/DOUT: D36.4 (DOUT), D37.2 (DIN)
/RGB_LED35/DOUT: D37.4 (DOUT), D38.2 (DIN)
/RGB_LED36/DOUT: D38.4 (DOUT), D39.2 (DIN)
/RGB_LED37/DOUT: D39.4 (DOUT), D40.2 (DIN)
/RGB_LED38/DOUT: D40.4 (DOUT), D41.2 (DIN)
/RGB_LED39/DOUT: D41.4 (DOUT), D42.2 (DIN)
/RGB_LED40/DOUT: D42.4 (DOUT), D43.2 (DIN)
/RGB_LED41/DOUT: D43.4 (DOUT), D45.2 (DIN)
/RGB_LED43/DOUT: D45.4 (DOUT), D57.2 (DIN)
/RGB_LED44/DIN: D46.2 (DIN), D56.4 (DOUT)
/RGB_LED45/DIN: D47.2 (DIN), D57.4 (DOUT)
/RGB_LED45/DOUT: D47.4 (DOUT), D48.2 (DIN)
/RGB_LED46/DOUT: D48.4 (DOUT), D49.2 (DIN)
/RGB_LED47/DOUT: D49.4 (DOUT), D50.2 (DIN)
/RGB_LED48/DOUT: D50.4 (DOUT), D51.2 (DIN)
/RGB_LED49/DOUT: D51.4 (DOUT), D52.2 (DIN)
/RGB_LED50/DOUT: D52.4 (DOUT), D53.2 (DIN)
/RGB_LED51/DOUT: D53.4 (DOUT), D54.2 (DIN)
/RGB_LED52/DOUT: D54.4 (DOUT), D55.2 (DIN)
/RGB_LED53/DOUT: D55.4 (DOUT), D56.2 (DIN)
/RGB_LED56/DOUT: D58.4 (DOUT), D59.2 (DIN)
/RGB_LED57/DOUT: D59.4 (DOUT), D60.2 (DIN)
/RGB_LED58/DOUT: D60.4 (DOUT), D61.2 (DIN)
/RGB_LED59/DOUT: D61.4 (DOUT), D62.2 (DIN)
/RGB_LED61/DIN: D63.2 (DIN), D64.4 (DOUT)
/RGB_LED62/DIN: D64.2 (DIN), D65.4 (DOUT)
/RGB_LED63/DIN: D65.2 (DIN), D66.4 (DOUT)
/RGB_LED64/DIN: D66.2 (DIN), D67.4 (DOUT)
/RGB_LED/DIN: D63.4 (DOUT); also elsewhere on the board
/RGB_LED/DOUT: D3.2 (DIN); also elsewhere on the board
GND: C2.2, C3.2, C4.2, C5.2, C6.2, C7.2, C8.2, C9.2, C10.2, C11.2, C12.2, C13.2, C14.2, C15.2, C16.2, C17.2, C18.2, C19.2, C20.2, C21.2, C22.2, C23.2, C24.2, C25.2, C26.2, C27.2, C28.2, C29.2, C30.2, C31.2, C32.2, C33.2, C34.2, C35.2, C36.2, C37.2, C38.2, C39.2, C40.2, C41.2, C42.2, C43.2, C44.2, C45.2, C46.2, C47.2, C48.2, C49.2, C50.2, C51.2, C52.2, C53.2, C54.2, C55.2, C56.2, C57.2, C58.2, C59.2, C60.2, C61.2, C62.2, C63.2, C64.2, C65.2, C66.2, C68.2, D3.1 (VSS), D4.1 (VSS), D5.1 (VSS), D6.1 (VSS), D7.1 (VSS), D8.1 (VSS), D9.1 (VSS), D10.1 (VSS), D11.1 (VSS), D12.1 (VSS), D13.1 (VSS), D14.1 (VSS), D15.1 (VSS), D16.1 (VSS), D17.1 (VSS), D18.1 (VSS), D19.1 (VSS), D20.1 (VSS), D21.1 (VSS), D22.1 (VSS), D23.1 (VSS), D24.1 (VSS), D25.1 (VSS), D26.1 (VSS), D27.1 (VSS), D28.1 (VSS), D29.1 (VSS), D30.1 (VSS), D31.1 (VSS), D32.1 (VSS), D33.1 (VSS), D34.1 (VSS), D35.1 (VSS), D36.1 (VSS), D37.1 (VSS), D38.1 (VSS), D39.1 (VSS), D40.1 (VSS), D41.1 (VSS), D42.1 (VSS), D43.1 (VSS), D44.1 (VSS), D45.1 (VSS), D46.1 (VSS), D47.1 (VSS), D48.1 (VSS), D49.1 (VSS), D50.1 (VSS), D51.1 (VSS), D52.1 (VSS), D53.1 (VSS), D54.1 (VSS), D55.1 (VSS), D56.1 (VSS), D57.1 (VSS), D58.1 (VSS), D59.1 (VSS), D60.1 (VSS), D61.1 (VSS), D62.1 (VSS), D63.1 (VSS), D64.1 (VSS), D65.1 (VSS), D66.1 (VSS), D67.1 (VSS), D126.1 (VSS); also elsewhere on the board
RGB: D67.2 (DIN); also elsewhere on the board

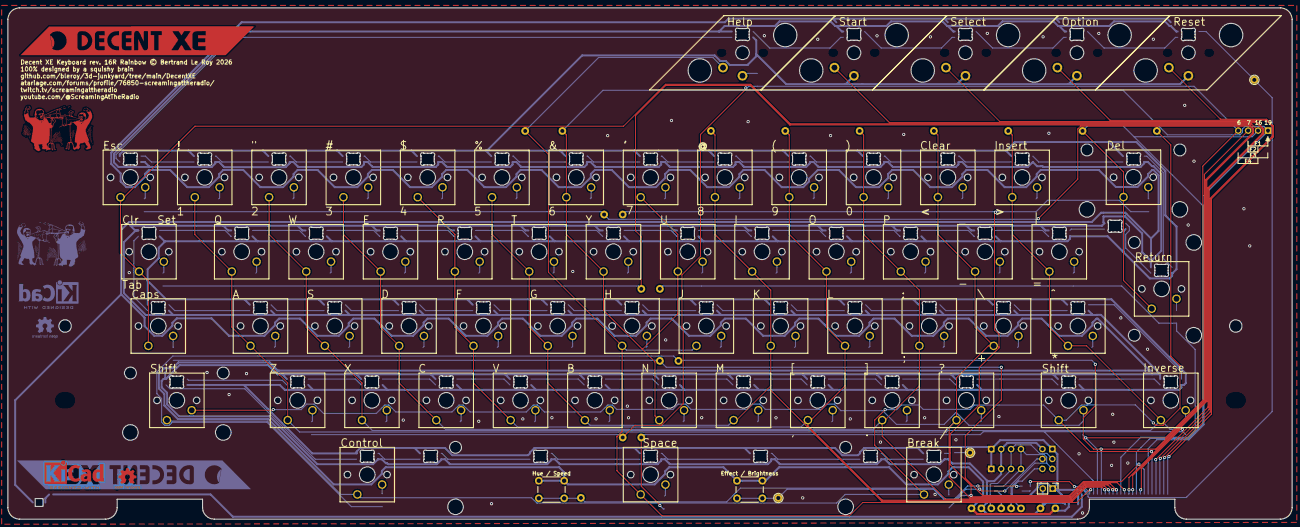
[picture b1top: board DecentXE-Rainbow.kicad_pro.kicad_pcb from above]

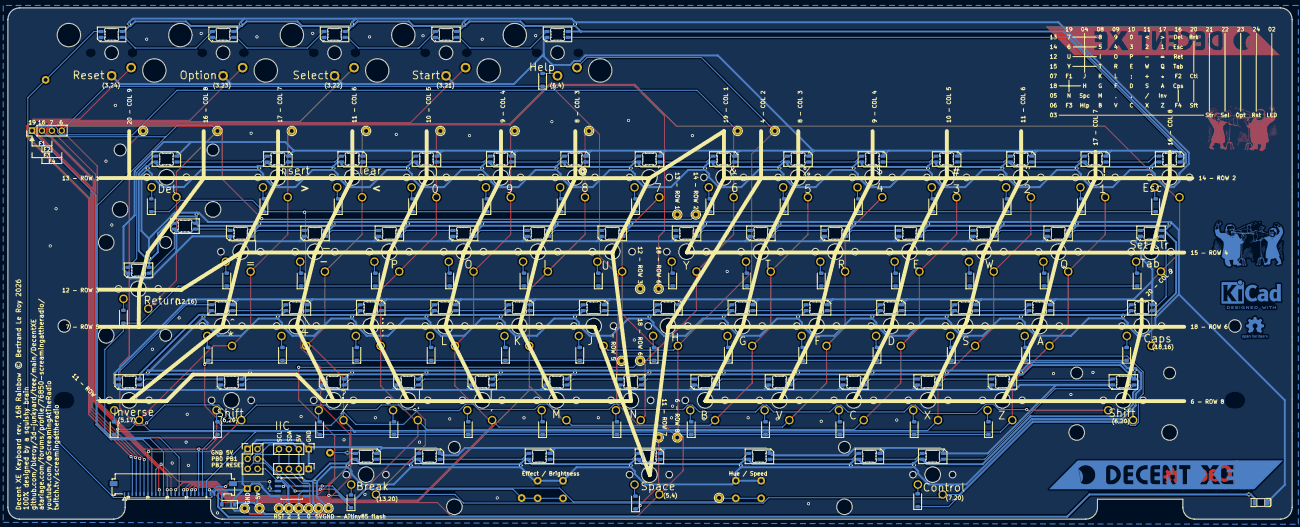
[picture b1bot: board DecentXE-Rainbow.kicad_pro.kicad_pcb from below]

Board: 2 copper layers, 329.2 x 131.1 mm, 301 parts (229 on the bottom side), 158 nets.

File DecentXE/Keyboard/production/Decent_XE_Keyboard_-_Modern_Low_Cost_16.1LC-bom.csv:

Designator,Footprint,Quantity,Value,LCSC Part #
"C1, C10, C11, C12, C13, C14, C15, C16, C17, C18, C19, C2, C20, C21, C22, C23, C24, C25, C26, C27, C28, C29, C3, C30, C31, C32, C33, C34, C35, C36, C37, C38, C39, C4, C40, C41, C42, C43, C44, C45, C46, C47, C48, C49, C5, C50, C51, C52, C53, C54, C55, C56, C57, C58, C59, C6, C60, C61, C62, C63, C64, C65, C66, C67, C7, C8, C9",0402,67,100nF,C1525
D1,LED1206-RD_RED_XL-3216SURC-FB,1,LED,C559117
"D10, D11, D12, D13, D14, D15, D16, D17, D18, D19, D2, D20, D21, D22, D23, D24, D25, D26, D27, D28, D29, D3, D30, D31, D32, D33, D34, D35, D36, D37, D38, D39, D4, D40, D41, D42, D43, D44, D45, D46, D47, D48, D49, D5, D50, D51, D52, D53, D54, D55, D56, D57, D58, D59, D6, D60, D61, D62, D63, D64, D65, D66, D67, D7, D8, D9",LED_SK6812MINI-E_3.2x2.8mm_P1.5mm_ReverseMount,66,SK6812MINI-E,C5378731
"D100, D101, D102, D103, D104, D105, D106, D107, D108, D109, D110, D111, D112, D113, D114, D115, D116, D117, D118, D119, D120, D121, D122, D123, D124, D68, D69, D70, D71, D72, D73, D74, D75, D76, D77, D78, D79, D80, D81, D82, D83, D84, D85, D86, D87, D88, D89, D90, D91, D92, D93, D94, D95, D96, D97, D98, D99",D_SOD-123,57,D,C81598
D125,D_SOD-123,1,D_Schottky,C8598
J2,Molex_200528-0260_1x26-1MP_P1.00mm_Horizontal,1,Conn_01x26,C2915299
"R1, R3",0402,2,470,C25117
R2,0402,1,100,C25076
STAB1,Choc-6-25U-Stab,1,6.25U,C193191
"STAB2, STAB3, STAB4, STAB5, STAB6",1.5U Atari Console Key Stabilizer holes,5,1.5U,
"SW0, SW1, SW2, SW3, SW4, SW5, SW6, SW7, SW8, SW9, SWA1, SWB1, SWBRK1, SWC1, SWCOMMA1, SWCPS1, SWCTL1, SWD1, SWDASH1, SWDEL1, SWE1, SWEQUAL1, SWESC1, SWF1, SWG1, SWGT1, SWH1, SWHLP1, SWI1, SWINV1, SWJ1, SWK1, SWL1, SWLEFTSFT1, SWLT1, SWM1, SWN1, SWO1, SWOPTION1, SWP1, SWPERIOD1, SWPLUS1, SWQ1, SWR1, SWRET1, SWRIGHTSFT1, SWS1, SWSELECT1, SWSEMI1, SWSLASH1, SWSPC1, SWSTAR1, SWSTART1, SWT1, SWTAB1, SWU1, SWV1, SWW1, SWX1, SWY1, SWZ1",Choc-1-00U,61,SW_Push,
"SW10, SW11",SW_PUSH_6mm,2,SW_Push,
SWRESET1,Choc-1-00U,1,SW_Push,C193191
U1,SOIC-8_5.3x5.3mm_P1.27mm,1,ATtiny85V-10S,C31540447

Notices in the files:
Decent400/Keyboard/Decent400-internal.kicad_pcb:
Decent 400 rev. 5 © Bertrand Le Roy 2026
Decent60/NavNumPad/DecentNumPad.kicad_pcb:
Decent60 DirNumPad Rev. 2 © Bertrand Le Roy 2026 github.com/bleroy/3d-junkyard/Decent60
Decent60 DirNumPad © Bertrand Le Roy 2026 github.com/bleroy/3d-junkyard/Decent60
DecentXE/Keyboard/DecentXE-LowCost.kicad_pcb:
Decent XE Keyboard rev. 16.1LC Modern Low Cost © Bertrand Le Roy 2026
DecentXE/Keyboard/DecentXE-Rainbow.kicad_pro.kicad_pcb:
Decent XE Keyboard rev. 16R Rainbow © Bertrand Le Roy 2026
DecentXE/readme.md:
Open source licenses
